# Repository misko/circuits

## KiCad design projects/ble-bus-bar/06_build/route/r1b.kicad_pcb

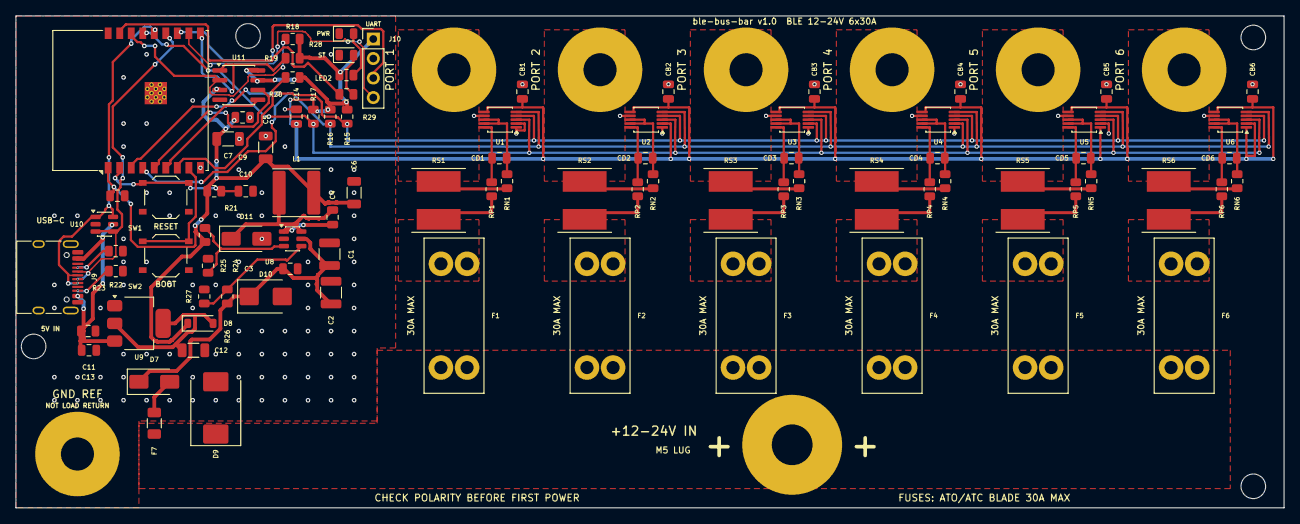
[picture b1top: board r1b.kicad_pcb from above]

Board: 2 copper layers, 165.0 x 64.0 mm, 101 parts (0 on the bottom side), 55 nets.

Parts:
C1, C2: 4u7 50V; C_1210_3225Metric
C3: 100n VIN; C_0805_2012Metric
C4: 100n boot; C_0805_2012Metric
C5, C6: 22u 3V3; C_1206_3216Metric
C7: 22u U7; C_1206_3216Metric
C8: 100n U7; C_0805_2012Metric
C9: 100n U11; C_0805_2012Metric
C10: 1u EN; C_0805_2012Metric
C11: 10u LDO in; C_0805_2012Metric
C12: 22u LDO out; C_1206_3216Metric
C13: 100n VUSB; C_0805_2012Metric
C14: 100n corridor 3V3; C_0805_2012Metric
CB1, CB2, CB3, CB4, CB5, CB6: 100n INA; C_0805_2012Metric
CD1, CD2, CD3, CD4, CD5, CD6: 100n diff; C_0805_2012Metric
D7: SS310 rev block; D_SMA
D8: B5819W OR; D_SOD-123
D9: SMCJ33A bus TVS; D_SMC
D10: SMBJ33A tap TVS; D_SMB
D11: SS310 catch; D_SMA
F1, F2, F3, F4, F5, F6: 3557-2 ATO 30A MAX; FuseHolder_Keystone_3557-2
F7: 0466002 2A; Fuse_1206_3216Metric
H1, H2, H3, H4: MountingHole_3.2mm_M3
J1: PORT 1 M4 LUG; Lug_M4
J2: PORT 2 M4 LUG; Lug_M4
J3: PORT 3 M4 LUG; Lug_M4
J4: PORT 4 M4 LUG; Lug_M4
J5: PORT 5 M4 LUG; Lug_M4
J6: PORT 6 M4 LUG; Lug_M4
J7: +12-24V IN M5 LUG; Lug_M5
J8: GND REF M4 LUG; Lug_M4
J9: TYPE-C-31-M-12; USB_C_Receptacle_HRO_TYPE-C-31-M-12
J10: DEBUG UART DNP; PinHeader_1x04_P2.54mm_Vertical
L1: 22u SWPA6045S; L_Sunlord_SWPA6045S
LED1: KT-0805G PWR; LED_0805_2012Metric
LED2: KT-0805G ST; LED_0805_2012Metric
R15: 4k7 SDA pu; R_0805_2012Metric
R16: 4k7 SCL pu; R_0805_2012Metric
R17: 10k ALERT pu; R_0805_2012Metric
R18: 10k IO2 pu; R_0805_2012Metric
R19: 10k CS pu; R_0805_2012Metric
R20: 10k IO8 pu; R_0805_2012Metric
R21: 10k EN pu; R_0805_2012Metric
R22: 5k1 CC1; R_0805_2012Metric
R23: 5k1 CC2; R_0805_2012Metric
R24: 33k FB hi; R_0805_2012Metric
R25: 10k FB lo; R_0805_2012Metric
R26: 560k UVLO hi; R_0805_2012Metric
R27: 100k UVLO lo; R_0805_2012Metric
R28: 2k PWR LED; R_0805_2012Metric
R29: 1k ST LED; R_0805_2012Metric
RN1, RN2, RN3, RN4, RN5, RN6: 10R sense-; R_0805_2012Metric
RP1, RP2, RP3, RP4, RP5, RP6: 10R sense+; R_0805_2012Metric
RS1, RS2, RS3, RS4, RS5, RS6: WSLP2726 0.5mR; R_Shunt_WSLP2726
SW1: RESET; SW_Push_1P1T_XKB_TS-1187A
SW2: BOOT; SW_Push_1P1T_XKB_TS-1187A
U1, U2, U3, U4, U5, U6: INA238AIDGSR; MSOP-10_3x3mm_P0.5mm
U7: ESP32-C3-WROOM-02-N4; ESP32-C3-WROOM-02_D03
U8: LMR16006XDDCR; TSOT-23-6
U9: AMS1117-3.3; SOT-223-3_TabPin2
U10: USBLC6-2SC6; SOT-23-6
U11: W25Q64JVSSIQ; SOIC-8_3.9x4.9mm_P1.27mm

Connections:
3V3: CB1.1, CB2.1, CB3.1, CB4.1, CB5.1, CB6.1, U1.6, U2.2, U2.6, U3.6, U4.6, U5.1, U5.6, U6.1, U6.2, U6.6
ALERT: R17.1, U1.3, U2.3, U3.3, U4.3, U5.3, U6.3, U7.15
BOOT: C4.1, U8.1
BOOT9: SW2.1, U7.8
CC1: J9.A5, R22.1
CC2: J9.B5, R23.1
EN: C10.1, R21.2, SW1.1, U7.2
FB: R24.2, R25.1, U8.3
FLASH_CS: R19.1, U7.10, U11.1
GND: C1.2, C2.2, C3.2, C5.2, C6.2, C7.2, C8.2, C9.2, C10.2, C11.2, C12.2, C13.2, C14.2, CB1.2, CB2.2, CB3.2, CB4.2, CB5.2, CB6.2, D9.2, D10.2, D11.2, J8.1, J9.A1, J9.A12, J9.B1, J9.B12, J9.SH, J10.2, LED1.1, LED2.1, R22.2, R23.2, R25.2, R27.2, SW1.2, SW2.2, U1.1, U1.2, U1.7, U2.1, U2.7, U3.1, U3.7, U4.1, U4.7, U5.2, U5.7, U6.7, U7.9, U7.19, U8.2, U9.1, U10.2, U11.4
IO8: R20.1, U7.7
KA1: CD1.1, RP1.2, U1.10
KA2: CD2.1, RP2.2, U2.10
KA3: CD3.1, RP3.2, U3.10
KA4: CD4.1, RP4.2, U4.10
KA5: CD5.1, RP5.2, U5.10
KA6: CD6.1, RP6.2, U6.10
KB1: CD1.2, RN1.2, U1.8, U1.9
KB2: CD2.2, RN2.2, U2.8, U2.9
KB3: CD3.2, RN3.2, U3.8, U3.9
KB4: CD4.2, RN4.2, U4.8, U4.9
KB5: CD5.2, RN5.2, U5.8, U5.9
KB6: CD6.2, RN6.2, U6.8, U6.9
LED1A: LED1.2, R28.2
LED2A: LED2.2, R29.2
LED_ST: R29.1, U7.17
RXD: J10.4, U7.11
SCL: R16.1, U1.5, U2.5, U3.5, U4.2, U4.5, U5.5, U6.5, U7.4
SDA: R15.1, U1.4, U2.4, U3.2, U3.4, U4.4, U5.4, U6.4, U7.3
SHDN: R26.2, R27.1, U8.4
SPI_CLK: U7.5, U11.6
SPI_MISO: R18.1, U7.16, U11.2
SPI_MOSI: U7.6, U11.5
SW: C4.2, D11.1, L1.1, U8.6
TMP_3V3: C5.1, C6.1, C7.1, C8.1, C9.1, C14.1, D8.1, J10.1, L1.2, R15.2, R16.2, R17.2, R18.2, R19.2, R20.2, R21.1, R24.1, R28.1, U7.1, U11.3, U11.7, U11.8
TXD: J10.3, U7.12
USB_DM: J9.A7, J9.B7, U7.13, U10.3, U10.4
USB_DP: J9.A6, J9.B6, U7.14, U10.1, U10.6
VBUS: D9.1, F1.1, F2.1, F3.1, F4.1, F5.1, F6.1, F7.1, J7.1
VF1: F1.2, RP1.1, RS1.1
VF2: F2.2, RP2.1, RS2.1
VF3: F3.2, RP3.1, RS3.1
VF4: F4.2, RP4.1, RS4.1
VF5: F5.2, RP5.1, RS5.1
VF6: F6.2, RP6.1, RS6.1
VIN_E: C1.1, C2.1, C3.1, D7.1, D10.1, R26.1, U8.5
VLDO: C12.1, D8.2, U9.2
VP1: J1.1, RN1.1, RS1.2
VP2: J2.1, RN2.1, RS2.2
VP3: J3.1, RN3.1, RS3.2
VP4: J4.1, RN4.1, RS4.2
VP5: J5.1, RN5.1, RS5.2
VP6: J6.1, RN6.1, RS6.2
VTAP: D7.2, F7.2
VUSB: C11.1, C13.1, J9.A4, J9.A9, J9.B4, J9.B9, U9.3, U10.5

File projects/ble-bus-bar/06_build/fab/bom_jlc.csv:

Comment,Designator,Footprint,MPN,LCSC
0466002 2A,F7,Fuse_1206_3216Metric,0466002.NRHF,C3105
100k UVLO lo,R27,R_0805_2012Metric,0805W8F1003T5E,C149504
100n,"C13,C14,C3,C4,C8,C9,CB1,CB2,CB3,CB4,CB5,CB6,CD1,CD2,CD3,CD4,CD5,CD6",C_0805_2012Metric,CC0805KRX7R9BB104,C49678
10R,"RN1,RN2,RN3,RN4,RN5,RN6,RP1,RP2,RP3,RP4,RP5,RP6",R_0805_2012Metric,0805W8F100JT5E,C17415
10k,"R17,R18,R19,R20,R21,R25",R_0805_2012Metric,0805W8F1002T5E,C17414
10u LDO in,C11,C_0805_2012Metric,CL21A106KAYNNNE,C15850
1k ST LED,R29,R_0805_2012Metric,0805W8F1001T5E,C17513
1u EN,C10,C_0805_2012Metric,CL21B105KBFNNNE,C28323
22u,"C12,C5,C6,C7",C_1206_3216Metric,CL31A226KAHNNNE,C12891
22u SWPA6045S,L1,L_Sunlord_SWPA6045S,SWPA6045S220MT,C83454
2k PWR LED,R28,R_0805_2012Metric,0805W8F2001T5E,C17604
33k FB hi,R24,R_0805_2012Metric,0805W8F3302T5E,C17633
3557-2 ATO 30A MAX,"F1,F2,F3,F4,F5,F6",FuseHolder_Keystone_3557-2,3557-2,
4k7,"R15,R16",R_0805_2012Metric,0805W8F4701T5E,C17673
4u7 50V,"C1,C2",C_1210_3225Metric,GRM32ER71H475KA88L,C86052
560k UVLO hi,R26,R_0805_2012Metric,0805W8F5603T5E,C15785
5k1,"R22,R23",R_0805_2012Metric,0805W8F5101T5E,C27834
AMS1117-3.3,U9,SOT-223-3_TabPin2,AMS1117-3.3,C6186
B5819W OR,D8,D_SOD-123,B5819W,C8598
BOOT / RESET,"SW1,SW2",SW_Push_1P1T_XKB_TS-1187A,TS-1187A-B-A-B,C318884
ESP32-C3-WROOM-02-N4,U7,ESP32-C3-WROOM-02_D03,ESP32-C3-WROOM-02-N4,C2934560
INA238AIDGSR,"U1,U2,U3,U4,U5,U6",MSOP-10_3x3mm_P0.5mm,INA238AIDGSR,C2868250
KT-0805G,"LED1,LED2",LED_0805_2012Metric,KT-0805G,C2297
LMR16006XDDCR,U8,TSOT-23-6,LMR16006XDDCR,C87080
SMBJ33A tap TVS,D10,D_SMB,SMBJ33A,C173526
SMCJ33A bus TVS,D9,D_SMC,SMCJ33A,C152083
SS310,"D11,D7",D_SMA,SS310,C15874
TYPE-C-31-M-12,J9,USB_C_Receptacle_HRO_TYPE-C-31-M-12,TYPE-C-31-M-12,C165948
USBLC6-2SC6,U10,SOT-23-6,USBLC6-2SC6,C2687116
W25Q64JVSSIQ,U11,SOIC-8_3.9x4.9mm_P1.27mm,W25Q64JVSSIQ,C179171
WSLP2726 0.5mR,"RS1,RS2,RS3,RS4,RS5,RS6",R_Shunt_WSLP2726,WSLP2726L5000FEA,C844297
